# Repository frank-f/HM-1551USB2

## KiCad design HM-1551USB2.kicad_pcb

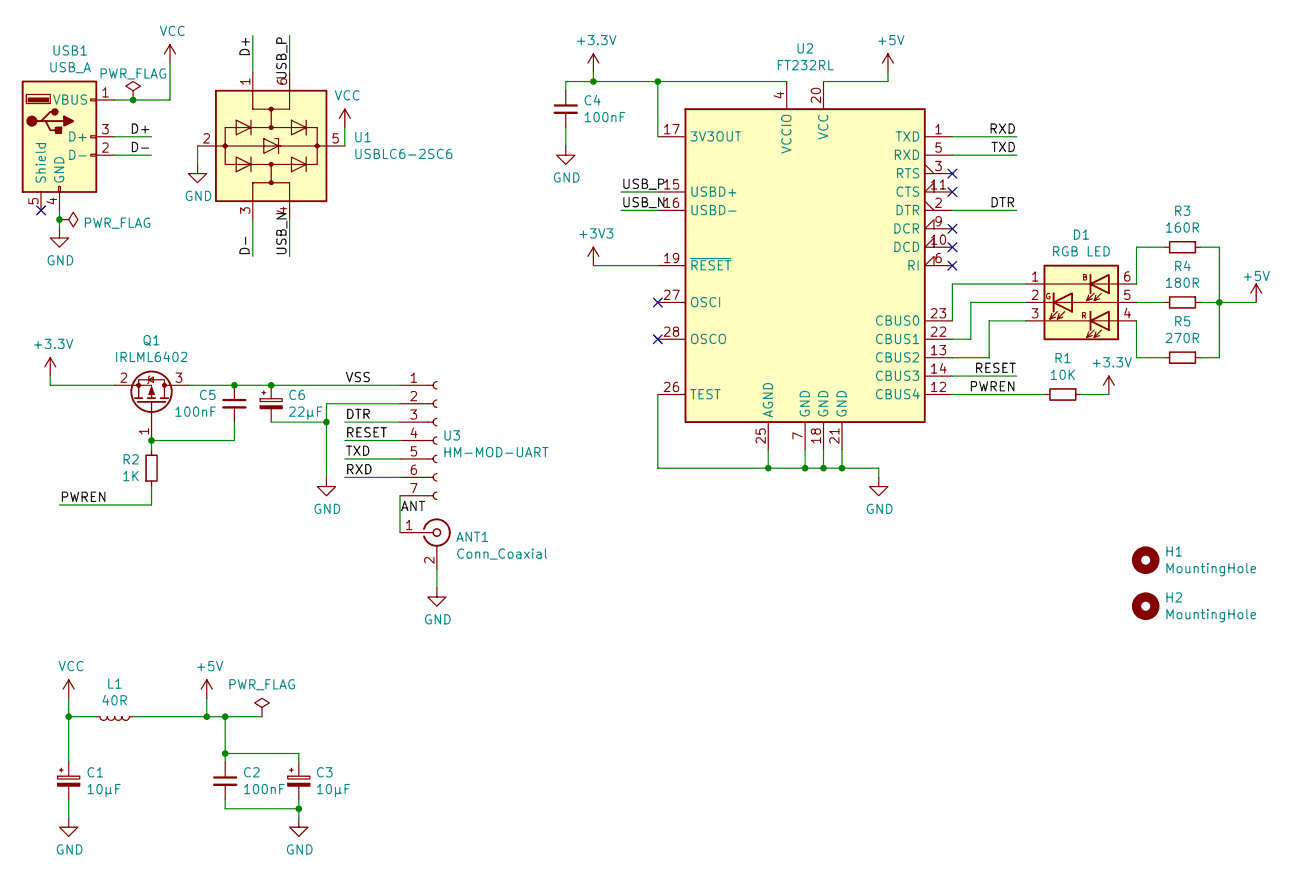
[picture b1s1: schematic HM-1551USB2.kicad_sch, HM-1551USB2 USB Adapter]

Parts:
ANT1: Conn_Coaxial; SMA-EdgeMount; LCSC C914558
C1, C3: 10µF; CP_EIA-3216-18_Kemet-A_Pad1.58x1.35mm_HandSolder; LCSC C7177
C2, C4, C5: 100nF; C_0805_2012Metric_Pad1.18x1.45mm_HandSolder; LCSC C307360
C6: 22µF; CP_EIA-6032-28_Kemet-C_Pad2.25x2.35mm_HandSolder; LCSC C130377
D1: RGB LED; LED_RGB_5050-6; LCSC C1322332
H1, H2: MountingHole; MountingHole_1.75mm
L1: 40R; L_0805_2012Metric_Pad1.15x1.40mm_HandSolder; LCSC C2661672
Q1: IRLML6402; SOT-23_Handsoldering; LCSC C2593
R1: 10K; R_0805_2012Metric_Pad1.20x1.40mm_HandSolder; LCSC C869153
R2: 1K; R_0805_2012Metric_Pad1.20x1.40mm_HandSolder; LCSC C144087
R3: 160R; R_0805_2012Metric_Pad1.20x1.40mm_HandSolder; LCSC C228326
R4: 180R; R_0805_2012Metric_Pad1.20x1.40mm_HandSolder; LCSC C228347
R5: 270R; R_0805_2012Metric_Pad1.20x1.40mm_HandSolder; LCSC C228675
U1: USBLC6-2SC6; SOT-23-6; LCSC C7519
U2: FT232RL; SSOP-28_5.3x10.2mm_P0.65mm; LCSC C8690
U3: HM-MOD-UART; HM-MOD-UART-SMT-REV
USB1: USB_A; USB 2.0 Type A; LCSC C46394

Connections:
+5V: C2.1, C3.1, L1.1, R3.1, R4.1, R5.1, U2.20 (VCC)
/ANT: ANT1.1 (In), U3.7
/D+: U1.1 (I/O1), USB1.3 (D+)
/D-: U1.3 (I/O2), USB1.2 (D-)
/DTR: U2.2 (DTR), U3.3
/PWREN: R1.2, R2.1, U2.12 (CBUS4)
/RESET: U2.14 (CBUS3), U3.4
/RXD: U2.1 (TXD), U3.6
/TXD: U2.5 (RXD), U3.5
/USB_N: U1.4 (I/O2), U2.16 (USBD-)
/USB_P: U1.6 (I/O1), U2.15 (USBD+)
/VSS: C5.1, C6.1, Q1.3 (D), U3.1
GND: ANT1.2 (Ext), C1.2, C2.2, C3.2, C4.2, C6.2, U1.2 (GND), U2.7 (GND), U2.18 (GND), U2.21 (GND), U2.25 (AGND), U2.26 (TEST), U3.2, USB1.4 (GND)
unnamed: C5.2, Q1.1 (G), R2.2
unnamed: D1.1 (KB), U2.23 (CBUS0)
unnamed: D1.2 (KG), U2.22 (CBUS1)
unnamed: D1.3 (KR), U2.13 (CBUS2)
unnamed: D1.4 (AR), R5.2
unnamed: D1.5 (AG), R4.2
unnamed: D1.6 (AB), R3.2
VCC: C1.1, L1.2, U1.5 (VBUS), USB1.1 (VBUS)

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
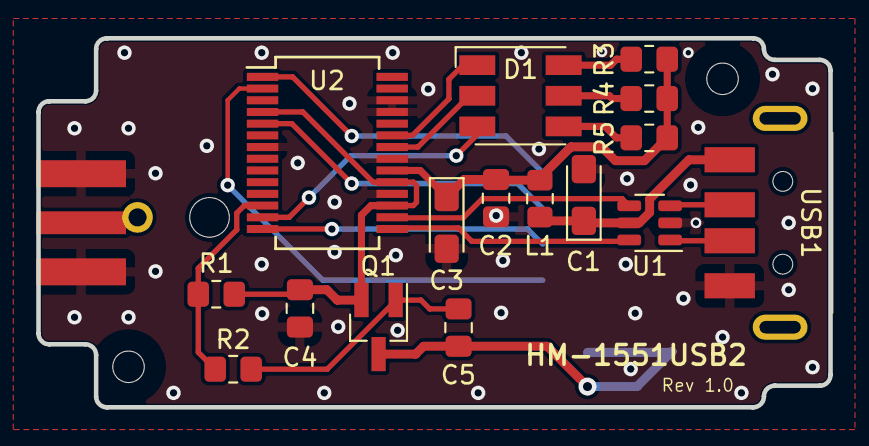
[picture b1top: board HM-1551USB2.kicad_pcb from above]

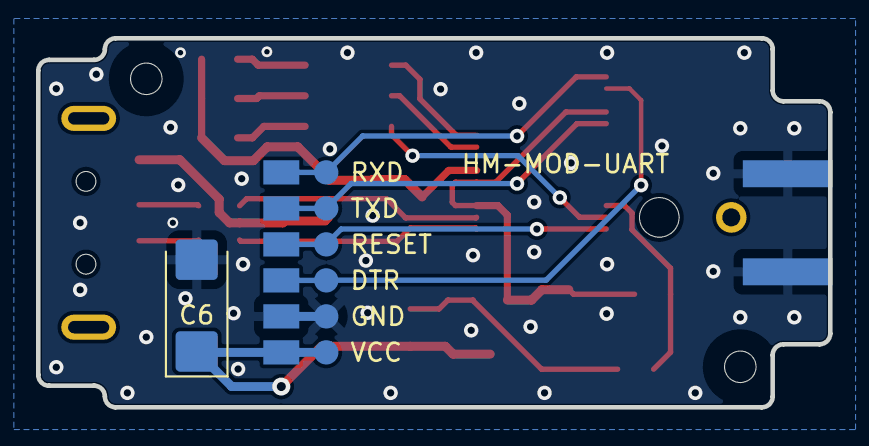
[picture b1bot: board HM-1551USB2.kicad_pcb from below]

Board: 2 copper layers, 44.0 x 20.5 mm, 21 parts (2 on the bottom side), 22 nets.

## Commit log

2022-01-26 First public version
2022-01-26 License under CC BY-NC-SA 4.0
2022-01-26 FT_PROG template for FT232R
2022-02-05 Remove H1 and ANT silkscreen
2022-03-12 Update component properties and fill BOM
